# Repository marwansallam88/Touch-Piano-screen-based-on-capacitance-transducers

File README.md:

# Touch Piano Screen Based On Capacitance Transducers

## Project Overview

### Technical Concept
A microcontroller-based electronic piano that utilizes capacitive sensing technology to replace traditional mechanical keys. The system employs RC time constant measurements to detect touch inputs with variable sensitivity, enabling:
- Contactless note triggering
- Pressure-sensitive volume control (future implementation)
- Compact form factor with minimal moving parts

### System Architecture
-
  ```mermaid
  graph TD
      A[Capacitive Touch Pads] --> B[RC Circuit]
      B --> C[Arduino Nano]
      C --> D[PWM Tone Generation]
      D --> E[Passive Buzzer]
      C --> F[LED Feedback]

## Key Specifications

| Parameter           | Specification         | Measurement Method     |
|---------------------|------------------------|-------------------------|
| Input Range         | 1–174 ms               | RC time constant        |
| Output Resolution   | 7,908 units            | 10-bit ADC              |
| Sensitivity         | 394.4 units/ms         | Linear regression       |
| Frequency Response  | 5.7–997.6 rad/s        | Bode analysis           |
| Power Consumption   | <100mA @ 5V            | Current probe           |

---

## Technical Implementation

### Sensing System

- 7× copper PCB pads (20mm² each)  
- 1MΩ current-limiting resistors  
- CapacitiveSensor library for Arduino

### Control Unit

- ATmega328P microcontroller  
- Custom PCB layout  
- 16MHz clock frequency

### Audio Output
- Passive piezoelectric buzzer  
- PWM-generated tones (C4–B4 frequency range)  
- 8Ω impedance

### Power Management
- 18650 Li-ion cell (3.7V nominal)  
- TP4056 charging module  
- MT3608 boost converter (to 5V)

---

## Performance Characteristics

### Transfer Function
-
    ```math
          H(s) = \frac{1}{\tau s + 1}, \quad \tau \in [0.001, 0.174] \text{ s}

### Bandwidth Variation

- **Untouched:** 997.6 rad/s (159 Hz)  
- **Fully pressed:** 5.7 rad/s (0.9 Hz)

---

## Statistical Analysis

| Metric                | Value             |
|------------------------|------------------|
| Resolution             | 7,908 units       |
| Sensitivity            | 394.4 units/ms    |
| Std. Deviation         | 3.12×10⁶          |
| Signal-to-Noise Ratio  | 42 dB             |

---

## Development Progress

### Research Phase
- Capacitive sensing literature review  
- Component selection analysis

### Prototyping
- Breadboard validation  
- Initial code development

### Production
- PCB design (Eagle)  
- SMT assembly process

### Validation
- Unit testing (per key)  
- Frequency response verification  
- Power consumption measurements

---

## Future Work

### Potential Implementations
- Pressure-sensitive volume control
- Multi-touch detection
- Octave expansion (14+ keys)
- Battery optimization for >24h runtime

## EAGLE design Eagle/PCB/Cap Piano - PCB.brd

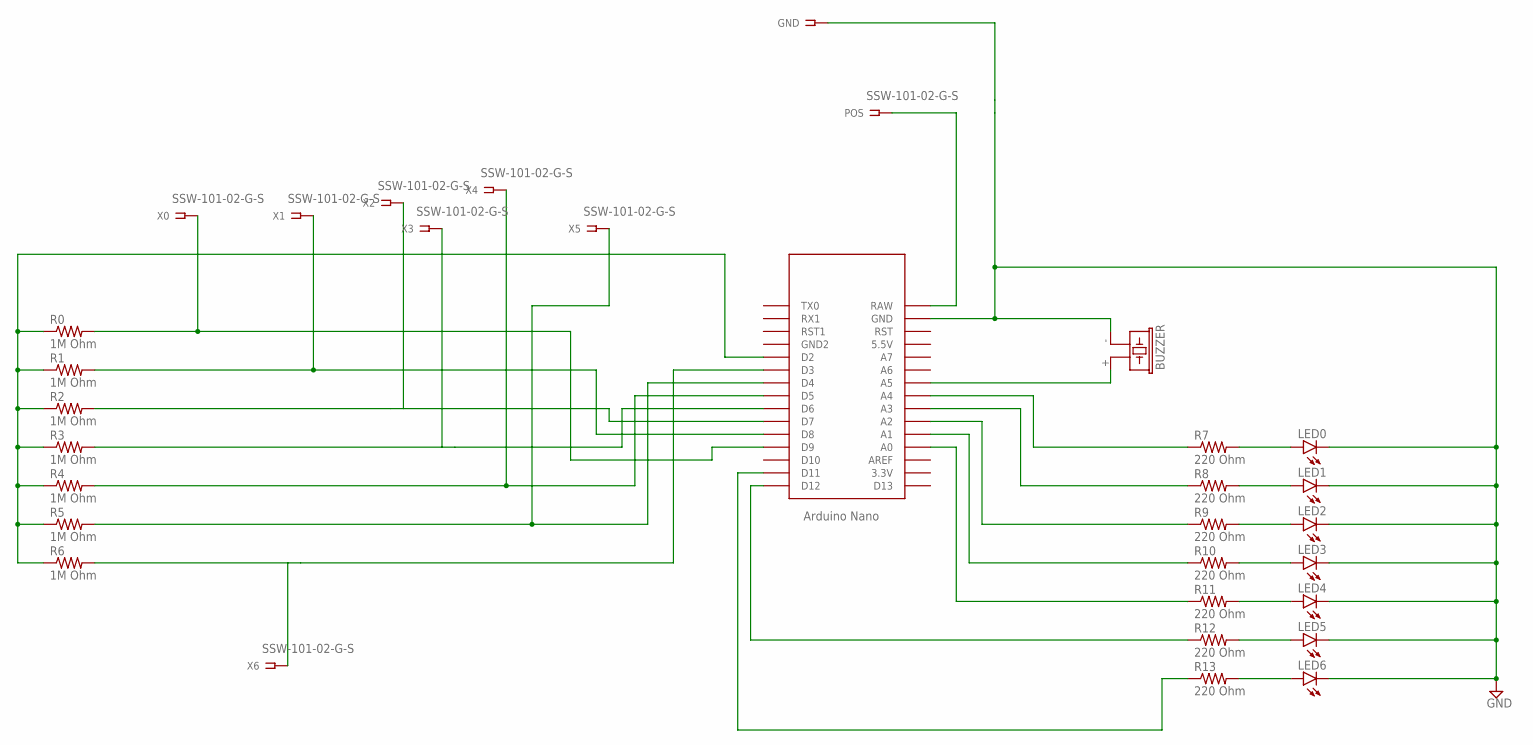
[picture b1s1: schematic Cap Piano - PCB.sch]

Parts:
BUZZER: F/CM12P
GND: SSW-101-02-G-S
LED0, LED1, LED2, LED3, LED4, LED5, LED6: LED5MM
POS: SSW-101-02-G-S
R0, R1, R2, R3, R4, R5, R6: 1M Ohm; 0207/12
R7, R8, R9, R10, R11, R12, R13: 220 Ohm; 0207/12
U$1: NANO
X0, X1, X2, X3, X4, X5, X6: SSW-101-02-G-S

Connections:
GND: BUZZER.- (2), GND.1, LED0.K (C), LED1.K (C), LED2.K (C), LED3.K (C), LED4.K (C), LED5.K (C), LED6.K (C), U$1.GND
unnamed: POS.1, U$1.RAW
unnamed: R5.2, U$1.D4, X5.1
unnamed: BUZZER.+ (1), U$1.A5
unnamed: R4.2, U$1.D5, X4.1
unnamed: R0.1, R1.1, R2.1, R3.1, R4.1, R5.1, R6.1, U$1.D2
unnamed: R6.2, U$1.D3, X6.1
unnamed: R3.2, U$1.D6, X3.1
unnamed: R2.2, U$1.D7, X2.1
unnamed: R1.2, U$1.D8, X1.1
unnamed: R0.2, U$1.D9, X0.1
unnamed: R13.1, U$1.D11
unnamed: R12.1, U$1.D12
unnamed: R11.1, U$1.A0
unnamed: R10.1, U$1.A1
unnamed: R9.1, U$1.A2
unnamed: R8.1, U$1.A3
unnamed: R7.1, U$1.A4
unnamed: LED0.A, R7.2
unnamed: LED1.A, R8.2
unnamed: LED2.A, R9.2
unnamed: LED3.A, R10.2
unnamed: LED4.A, R11.2
unnamed: LED5.A, R12.2
unnamed: LED6.A, R13.2

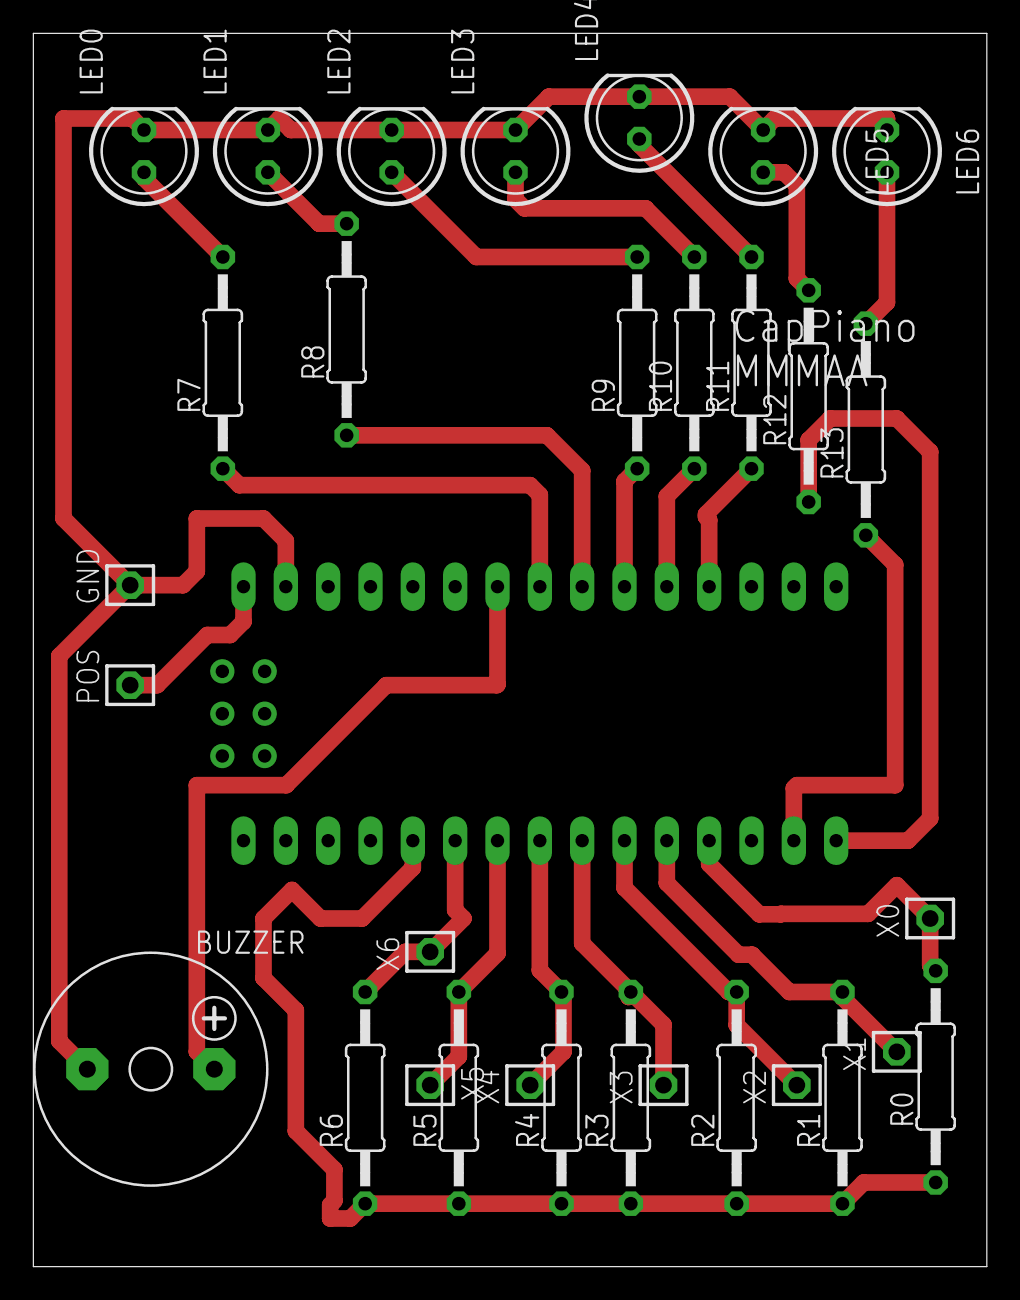
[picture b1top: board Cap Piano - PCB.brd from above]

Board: 2 copper layers, 57.2 x 74.0 mm, 32 parts (0 on the bottom side), 25 nets.

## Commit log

2023-01-23 Create e
2025-06-04 Rename Cap_Piano.jpg to Photos/Cap_Piano.jpg
2025-06-04 Rename Cap_Piano_Circuit.png to Photos/Cap_Piano_Circuit.png
2025-06-04 Rename Cap_Piano_PCB.png to Photos/Cap_Piano_PCB.png
